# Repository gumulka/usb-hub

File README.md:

# USB Hub

A simple USB 2.0 USB-Hub, with physical buttons to toggle the power to
the port as well as an usb interface to toggle the different ports.

## Compile firmware

The firmware is written with [zephyr](zephyr).
Click [here](zephyr_getting_started) for information on how to
[get started](zephyr_getting_started).

With zephyr and west installed execute the following to compile and flash the
firmware with debug information.

```bash
west init -m https://github.com/gumulka/usb-hub --mr zephyr usb-hub
cd usb-hub
west update
cd usb-hub
west build -p -b fabians_usb_hub app -- -DOVERLAY_CONFIG="debug.conf"
west flash
```

## Compile the bootloader

The bootloader uses a lot of memory and needs some special attention to get it
to work. We are nearing the limit of what the STM32 can do and process.

Compile and flash it with the following commands:

```bash
west build -p -b fabians_usb_hub -d build_mcuboot ../bootloader/mcuboot/boot/zephyr/ -- -DOVERLAY_CONFIG="`pwd`/mcuboot.conf"
west flash -d build_mcuboot
```

[zephyr]: https://github.com/zephyrproject-rtos/zephyr
[zephyr_getting_started]: https://docs.zephyrproject.org/latest/develop/getting_started/index.html

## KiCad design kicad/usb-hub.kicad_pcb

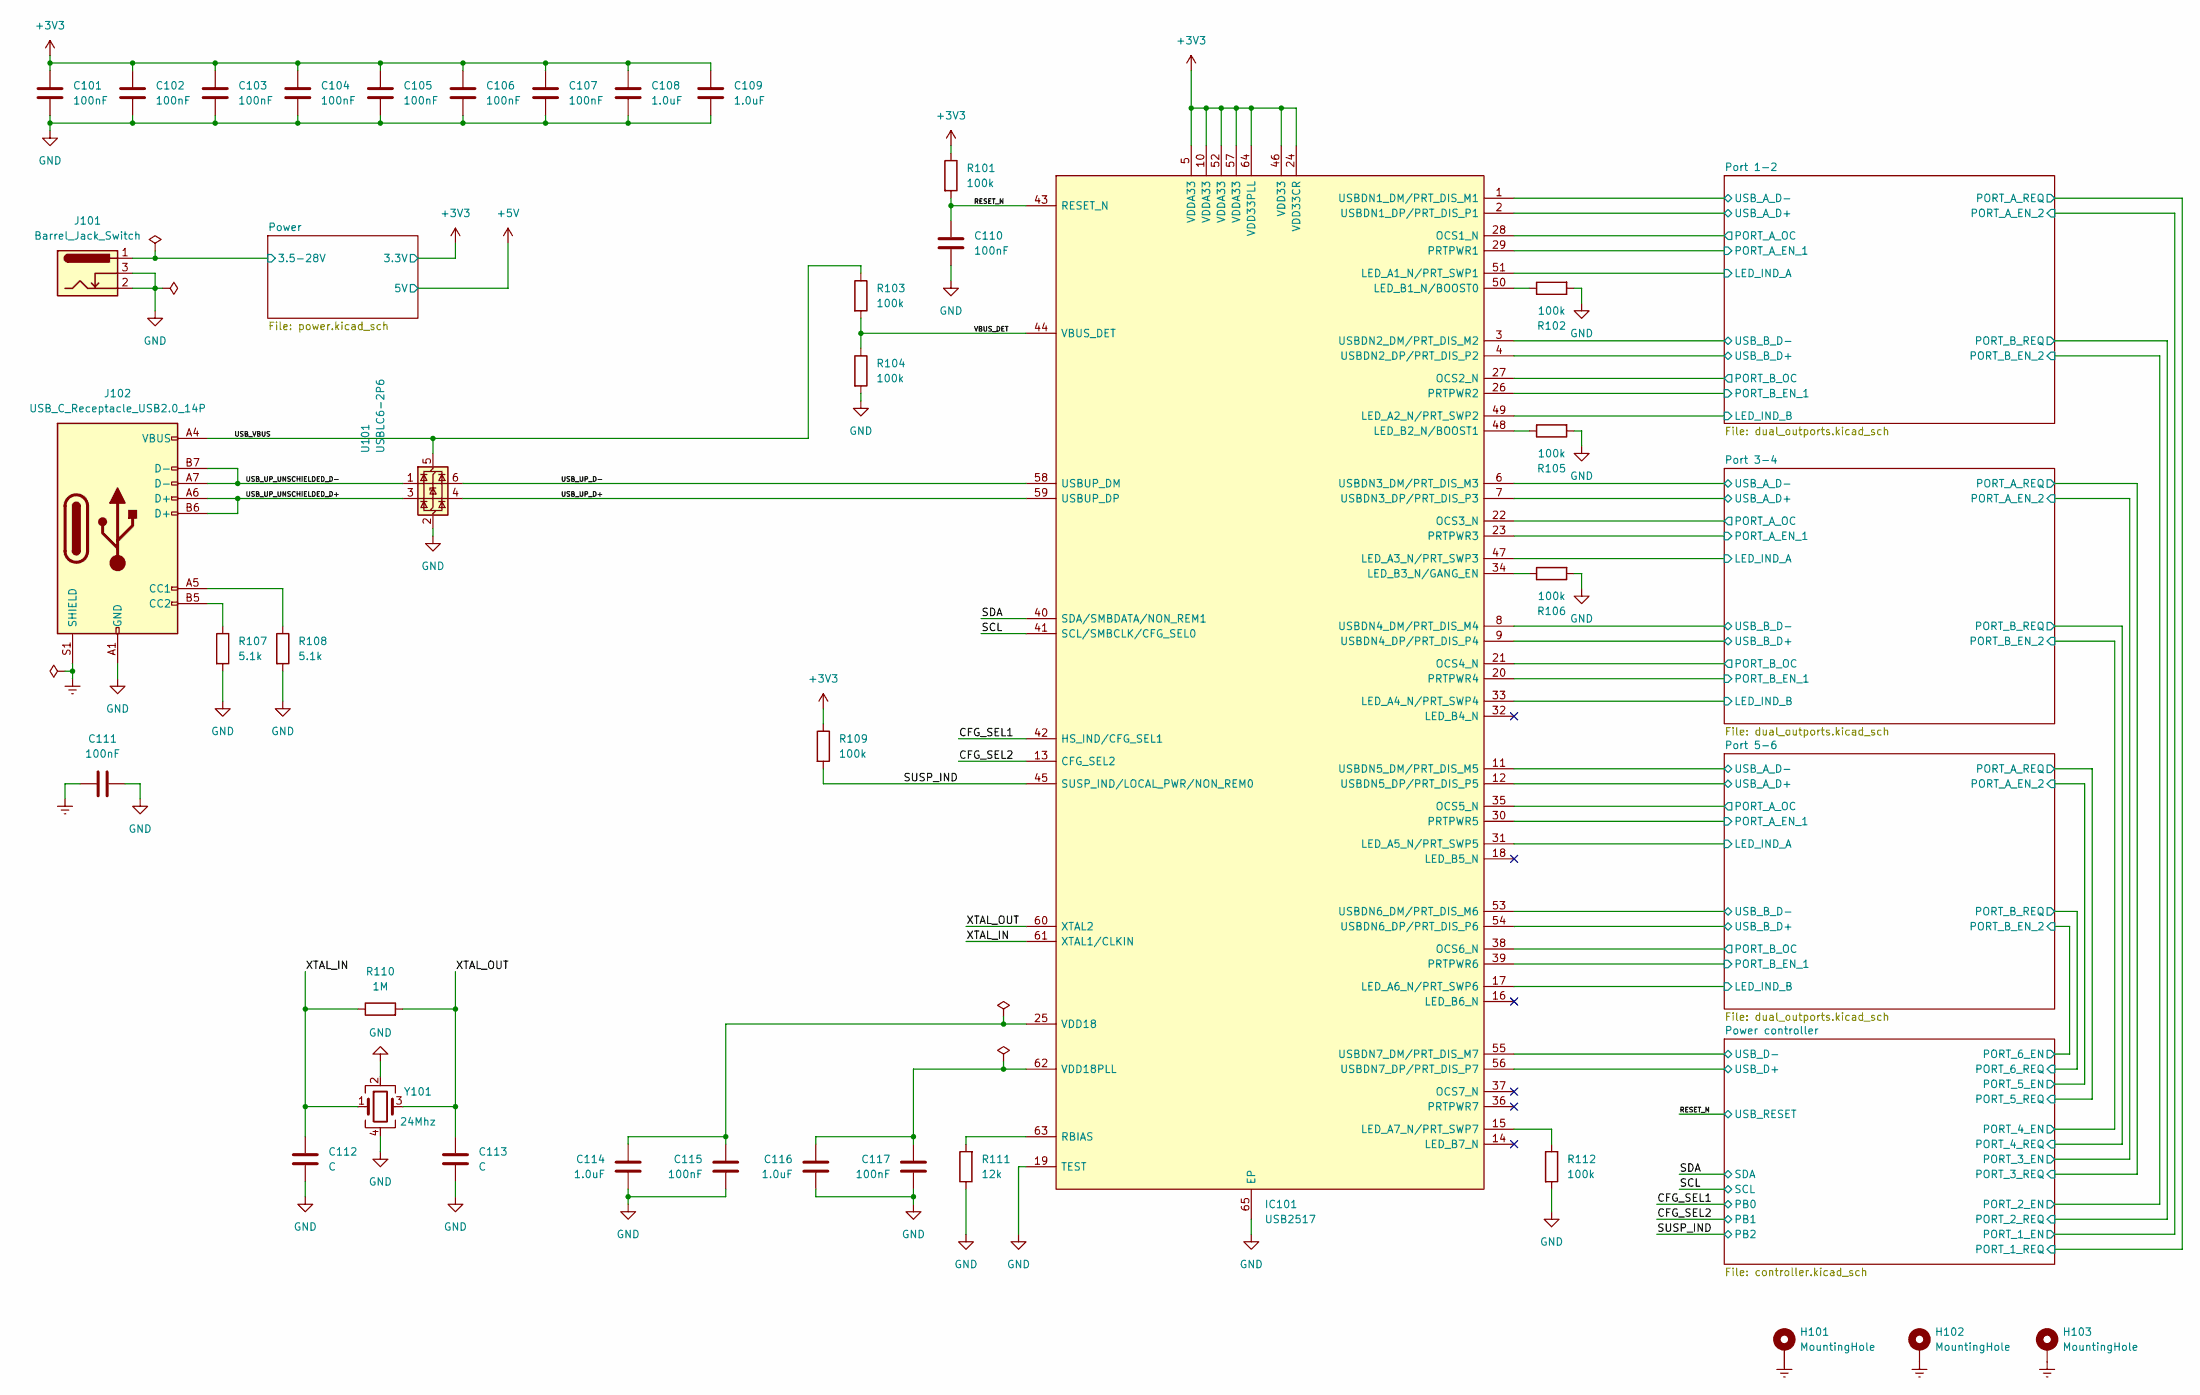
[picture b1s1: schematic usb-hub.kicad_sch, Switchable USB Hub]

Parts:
C101, C102, C103, C104, C105, C106, C107, C110, C111, C115, C117: 100nF; C_0402_1005Metric; LCSC# C307331
C108, C109, C114, C116: 1.0uF; C_0603_1608Metric; LCSC# C15849
C112, C113: C; C_0402_1005Metric
H101, H102, H103: MountingHole; MountingHole_3.2mm_M3_Pad_Via
IC101: USB2517; QFN-64-1EP_9x9mm_P0.5mm_EP4.7x4.7mm_ThermalVias; MPN USB2517; LCSC# C626668
J101: Barrel_Jack_Switch; BarrelJack_Wuerth_6941xx301002; MPN 694106301002
J102: USB_C_Receptacle_USB2.0_14P; USB_C_Receptacle_G-Switch_GT-USB-7010ASV; LCSC# C2988369
R101, R102, R103, R104, R105, R106, R109, R112: 100k; R_0402_1005Metric; MPN 100K; LCSC# C25741
R107, R108: 5.1k; R_0402_1005Metric; MPN 5,1K; LCSC# C25905
R110: 1M; R_0402_1005Metric; MPN 1M; LCSC# C26083
R111: 12k; R_0402_1005Metric; MPN 12K; LCSC# C25752
U101: USBLC6-2P6; SOT-666; MPN USBLC6-2P6; LCSC# C2827693
Y101: 24Mhz; Crystal_SMD_3225-4Pin_3.2x2.5mm; LCSC# C70590

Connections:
+3V3: C101.1, C102.1, C103.1, C104.1, C105.1, C106.1, C107.1, C108.1, C109.1, IC101.5 (VDDA33), IC101.10 (VDDA33), IC101.24 (VDD33CR), IC101.46 (VDD33), IC101.52 (VDDA33), IC101.57 (VDDA33), IC101.64 (VDD33PLL), R101.1, R109.1; also elsewhere on the board
/CFG_SEL1: IC101.42 (HS_IND/CFG_SEL1); also elsewhere on the board
/CFG_SEL2: IC101.13 (CFG_SEL2); also elsewhere on the board
/Port 1-2/LED_IND_A: IC101.51 (LED_A1_N/PRT_SWP1); also elsewhere on the board
/Port 1-2/LED_IND_B: IC101.49 (LED_A2_N/PRT_SWP2); also elsewhere on the board
/Port 1-2/PORT_A_EN_1: IC101.29 (PRTPWR1); also elsewhere on the board
/Port 1-2/PORT_A_OC: IC101.28 (OCS1_N); also elsewhere on the board
/Port 1-2/PORT_B_EN_1: IC101.26 (PRTPWR2); also elsewhere on the board
/Port 1-2/PORT_B_OC: IC101.27 (OCS2_N); also elsewhere on the board
/Port 1-2/USB_A_D+: IC101.2 (USBDN1_DP/PRT_DIS_P1); also elsewhere on the board
/Port 1-2/USB_A_D-: IC101.1 (USBDN1_DM/PRT_DIS_M1); also elsewhere on the board
/Port 1-2/USB_B_D+: IC101.4 (USBDN2_DP/PRT_DIS_P2); also elsewhere on the board
/Port 1-2/USB_B_D-: IC101.3 (USBDN2_DM/PRT_DIS_M2); also elsewhere on the board
/Port 3-4/LED_IND_A: IC101.47 (LED_A3_N/PRT_SWP3); also elsewhere on the board
/Port 3-4/LED_IND_B: IC101.33 (LED_A4_N/PRT_SWP4); also elsewhere on the board
/Port 3-4/PORT_A_EN_1: IC101.23 (PRTPWR3); also elsewhere on the board
/Port 3-4/PORT_A_OC: IC101.22 (OCS3_N); also elsewhere on the board
/Port 3-4/PORT_B_EN_1: IC101.20 (PRTPWR4); also elsewhere on the board
/Port 3-4/PORT_B_OC: IC101.21 (OCS4_N); also elsewhere on the board
/Port 3-4/USB_A_D+: IC101.7 (USBDN3_DP/PRT_DIS_P3); also elsewhere on the board
/Port 3-4/USB_A_D-: IC101.6 (USBDN3_DM/PRT_DIS_M3); also elsewhere on the board
/Port 3-4/USB_B_D+: IC101.9 (USBDN4_DP/PRT_DIS_P4); also elsewhere on the board
/Port 3-4/USB_B_D-: IC101.8 (USBDN4_DM/PRT_DIS_M4); also elsewhere on the board
/Port 5-6/LED_IND_A: IC101.31 (LED_A5_N/PRT_SWP5); also elsewhere on the board
/Port 5-6/LED_IND_B: IC101.17 (LED_A6_N/PRT_SWP6); also elsewhere on the board
/Port 5-6/PORT_A_EN_1: IC101.30 (PRTPWR5); also elsewhere on the board
/Port 5-6/PORT_A_OC: IC101.35 (OCS5_N); also elsewhere on the board
/Port 5-6/PORT_B_EN_1: IC101.39 (PRTPWR6); also elsewhere on the board
/Port 5-6/PORT_B_OC: IC101.38 (OCS6_N); also elsewhere on the board
/Port 5-6/USB_A_D+: IC101.12 (USBDN5_DP/PRT_DIS_P5); also elsewhere on the board
/Port 5-6/USB_A_D-: IC101.11 (USBDN5_DM/PRT_DIS_M5); also elsewhere on the board
/Port 5-6/USB_B_D+: IC101.54 (USBDN6_DP/PRT_DIS_P6); also elsewhere on the board
/Port 5-6/USB_B_D-: IC101.53 (USBDN6_DM/PRT_DIS_M6); also elsewhere on the board
/Power controller/USB_D+: IC101.56 (USBDN7_DP/PRT_DIS_P7); also elsewhere on the board
/Power controller/USB_D-: IC101.55 (USBDN7_DM/PRT_DIS_M7); also elsewhere on the board
/Power/3.5-28V: J101.1; also elsewhere on the board
/RESET_N: C110.1, IC101.43 (RESET_N), R101.2; also elsewhere on the board
/SCL: IC101.41 (SCL/SMBCLK/CFG_SEL0); also elsewhere on the board
/SDA: IC101.40 (SDA/SMBDATA/NON_REM1); also elsewhere on the board
/SUSP_IND: IC101.45 (SUSP_IND/LOCAL_PWR/NON_REM0), R109.2; also elsewhere on the board
/USB_UP_D+: IC101.59 (USBUP_DP), U101.4 (I/O2)
/USB_UP_D-: IC101.58 (USBUP_DM), U101.6 (I/O1)
/USB_UP_UNSCHIELDED_D+: J102.A6 (D+), J102.B6 (D+), U101.3 (I/O2)
/USB_UP_UNSCHIELDED_D-: J102.A7 (D-), J102.B7 (D-), U101.1 (I/O1)
/USB_VBUS: J102.A4 (VBUS), J102.A9 (VBUS), J102.B4 (VBUS), J102.B9 (VBUS), R103.1, U101.5 (VBUS)
/VBUS_DET: IC101.44 (VBUS_DET), R103.2, R104.1
/XTAL_IN: C112.1, IC101.61 (XTAL1/CLKIN), R110.1, Y101.1
/XTAL_OUT: C113.1, IC101.60 (XTAL2), R110.2, Y101.3
Earth: C111.2, H101.1, H102.1, H103.1, J102.S1 (SHIELD); also elsewhere on the board
GND: C101.2, C102.2, C103.2, C104.2, C105.2, C106.2, C107.2, C108.2, C109.2, C110.2, C111.1, C112.2, C113.2, C114.2, C115.2, C116.2, C117.2, IC101.19 (TEST), IC101.65 (EP), J101.2, J101.3, J102.A1 (GND), J102.A12 (GND), J102.B1 (GND), J102.B12 (GND), R102.2, R104.2, R105.2, R106.2, R107.2, R108.2, R111.1, R112.2, U101.2 (GND), Y101.2, Y101.4; also elsewhere on the board
unnamed: IC101.15 (LED_A7_N/PRT_SWP7), R112.1
unnamed: IC101.50 (LED_B1_N/BOOST0), R102.1
unnamed: IC101.48 (LED_B2_N/BOOST1), R105.1
unnamed: IC101.34 (LED_B3_N/GANG_EN), R106.1
unnamed: IC101.63 (RBIAS), R111.2
unnamed: C114.1, C115.1, IC101.25 (VDD18)
unnamed: C116.1, C117.1, IC101.62 (VDD18PLL)
unnamed: J102.A5 (CC1), R108.1
unnamed: J102.B5 (CC2), R107.1

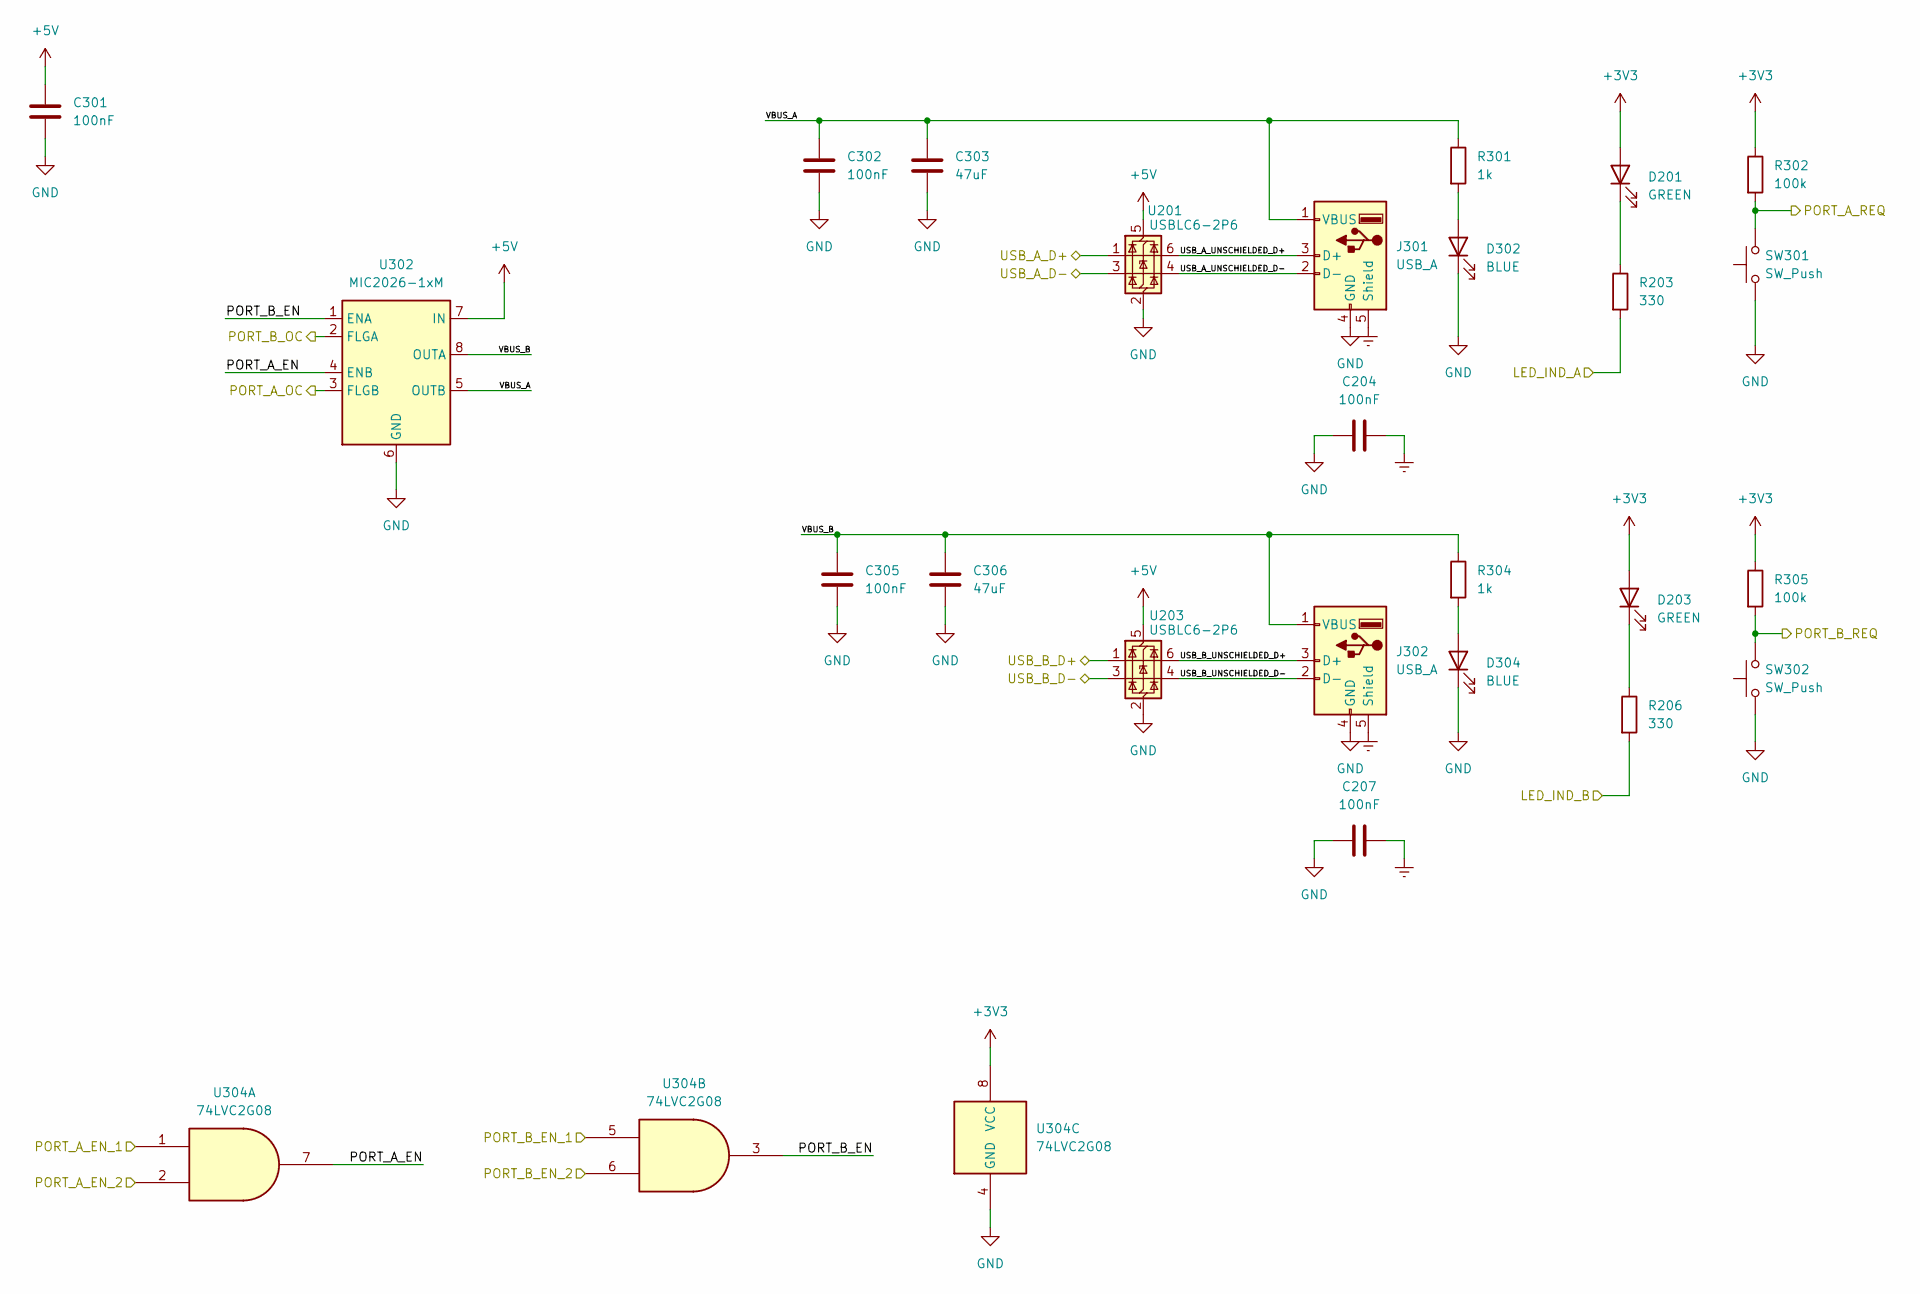
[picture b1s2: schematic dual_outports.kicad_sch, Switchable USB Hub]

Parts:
C204, C207, C301, C302, C305: 100nF; C_0402_1005Metric; LCSC# C307331
C303, C306: 47uF; C_0805_2012Metric; LCSC# C16780
D201, D203: GREEN; LED_0603_1608Metric; LCSC# C2986059
D302, D304: BLUE; LED_0603_1608Metric; LCSC# C72041
J301, J302: USB_A; UJ2-AV-W4-TH; MPN UJ2-AV-W4-TH
R203, R206: 330; R_0402_1005Metric; MPN 330R; LCSC# C25104
R301, R304: 1k; R_0402_1005Metric; MPN 1k; LCSC# C11702
R302, R305: 100k; R_0402_1005Metric; MPN 100K; LCSC# C25741
SW301, SW302: SW_Push; SW_SPST_TL3342; LCSC# C318884
U201, U203: USBLC6-2P6; SOT-666; MPN USBLC6-2P6; LCSC# C2827693
U302: MIC2026-1xM; SOIC-8_3.9x4.9mm_P1.27mm; MPN MIC2026-1YM; LCSC# C144190
U304: 74LVC2G08; VSSOP-8_2.3x2mm_P0.5mm; MPN 74LVC2G08; LCSC# C91875

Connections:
+3V3: D201.2 (A), D203.2 (A), R302.1, R305.1, U304.8 (VCC); also elsewhere on the board
+5V: C301.1, U201.5 (VBUS), U203.5 (VBUS), U302.7 (IN); also elsewhere on the board
/Port 1-2/LED_IND_A: R203.2; also elsewhere on the board
/Port 1-2/LED_IND_B: R206.2; also elsewhere on the board
/Port 1-2/USB_A_D+: U201.1 (I/O1); also elsewhere on the board
/Port 1-2/USB_A_D-: U201.3 (I/O2); also elsewhere on the board
/Port 1-2/USB_B_D+: U203.1 (I/O1); also elsewhere on the board
/Port 1-2/USB_B_D-: U203.3 (I/O2); also elsewhere on the board
/Port 3-4/PORT_A_EN: U302.4 (ENB), U304.7
/Port 3-4/PORT_A_EN_1: U304.1; also elsewhere on the board
/Port 3-4/PORT_A_EN_2: U304.2; also elsewhere on the board
/Port 3-4/PORT_A_OC: U302.3 (FLGB); also elsewhere on the board
/Port 3-4/PORT_A_REQ: R302.2, SW301.2; also elsewhere on the board
/Port 3-4/PORT_B_EN: U302.1 (ENA), U304.3
/Port 3-4/PORT_B_EN_1: U304.5; also elsewhere on the board
/Port 3-4/PORT_B_EN_2: U304.6; also elsewhere on the board
/Port 3-4/PORT_B_OC: U302.2 (FLGA); also elsewhere on the board
/Port 3-4/PORT_B_REQ: R305.2, SW302.2; also elsewhere on the board
/Port 3-4/VBUS_A: C302.1, C303.1, J301.1 (VBUS), R301.1, U302.5 (OUTB)
/Port 3-4/VBUS_B: C305.1, C306.1, J302.1 (VBUS), R304.1, U302.8 (OUTA)
Earth: C204.2, C207.2, J301.5 (Shield), J302.5 (Shield); also elsewhere on the board
GND: C204.1, C207.1, C301.2, C302.2, C303.2, C305.2, C306.2, D302.1 (K), D304.1 (K), J301.4 (GND), J302.4 (GND), SW301.1, SW302.1, U201.2 (GND), U203.2 (GND), U302.6 (GND), U304.4 (GND); also elsewhere on the board
unnamed: D201.1 (K), R203.1
unnamed: D203.1 (K), R206.1
unnamed: D302.2 (A), R301.2
unnamed: D304.2 (A), R304.2

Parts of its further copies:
C201, C202, C205, C304, C307, C401, C402, C404, C405, C407: 100nF; C_0402_1005Metric; LCSC# C307331
C203, C206, C403, C406: 47uF; C_0805_2012Metric; LCSC# C16780
D202, D204, D402, D404: BLUE; LED_0603_1608Metric; LCSC# C72041
D301, D303, D401, D403: GREEN; LED_0603_1608Metric; LCSC# C2986059
J201, J202, J401, J402: USB_A; UJ2-AV-W4-TH; MPN UJ2-AV-W4-TH
R201, R204, R401, R404: 1k; R_0402_1005Metric; MPN 1k; LCSC# C11702
R202, R205, R402, R405: 100k; R_0402_1005Metric; MPN 100K; LCSC# C25741
R303, R306, R403, R406: 330; R_0402_1005Metric; MPN 330R; LCSC# C25104
SW201, SW202, SW401, SW402: SW_Push; SW_SPST_TL3342; LCSC# C318884
U202, U402: MIC2026-1xM; SOIC-8_3.9x4.9mm_P1.27mm; MPN MIC2026-1YM; LCSC# C144190
U204, U404: 74LVC2G08; VSSOP-8_2.3x2mm_P0.5mm; MPN 74LVC2G08; LCSC# C91875
U301, U303, U401, U403: USBLC6-2P6; SOT-666; MPN USBLC6-2P6; LCSC# C2827693

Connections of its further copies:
+3V3: D301.2 (A), D303.2 (A), D401.2 (A), D403.2 (A), R202.1, R205.1, R402.1, R405.1, U204.8 (VCC), U404.8 (VCC); also elsewhere on the board
+5V: C201.1, C401.1, U202.7 (IN), U301.5 (VBUS), U303.5 (VBUS), U401.5 (VBUS), U402.7 (IN), U403.5 (VBUS); also elsewhere on the board
/Port 1-2/PORT_A_EN: U202.4 (ENB), U204.7
/Port 1-2/PORT_A_EN_1: U204.1; also elsewhere on the board
/Port 1-2/PORT_A_EN_2: U204.2; also elsewhere on the board
/Port 1-2/PORT_A_OC: U202.3 (FLGB); also elsewhere on the board
/Port 1-2/PORT_A_REQ: R202.2, SW201.2; also elsewhere on the board
/Port 1-2/PORT_B_EN: U202.1 (ENA), U204.3
/Port 1-2/PORT_B_EN_1: U204.5; also elsewhere on the board
/Port 1-2/PORT_B_EN_2: U204.6; also elsewhere on the board
/Port 1-2/PORT_B_OC: U202.2 (FLGA); also elsewhere on the board
/Port 1-2/PORT_B_REQ: R205.2, SW202.2; also elsewhere on the board
/Port 1-2/VBUS_A: C202.1, C203.1, J201.1 (VBUS), R201.1, U202.5 (OUTB)
/Port 1-2/VBUS_B: C205.1, C206.1, J202.1 (VBUS), R204.1, U202.8 (OUTA)
/Port 3-4/LED_IND_A: R303.2; also elsewhere on the board
/Port 3-4/LED_IND_B: R306.2; also elsewhere on the board
/Port 3-4/USB_A_D+: U301.1 (I/O1); also elsewhere on the board
/Port 3-4/USB_A_D-: U301.3 (I/O2); also elsewhere on the board
/Port 3-4/USB_B_D+: U303.1 (I/O1); also elsewhere on the board
/Port 3-4/USB_B_D-: U303.3 (I/O2); also elsewhere on the board
/Port 5-6/LED_IND_A: R403.2; also elsewhere on the board
/Port 5-6/LED_IND_B: R406.2; also elsewhere on the board
/Port 5-6/PORT_A_EN: U402.4 (ENB), U404.7
/Port 5-6/PORT_A_EN_1: U404.1; also elsewhere on the board
/Port 5-6/PORT_A_EN_2: U404.2; also elsewhere on the board
/Port 5-6/PORT_A_OC: U402.3 (FLGB); also elsewhere on the board
/Port 5-6/PORT_A_REQ: R402.2, SW401.2; also elsewhere on the board
/Port 5-6/PORT_B_EN: U402.1 (ENA), U404.3
/Port 5-6/PORT_B_EN_1: U404.5; also elsewhere on the board
/Port 5-6/PORT_B_EN_2: U404.6; also elsewhere on the board
/Port 5-6/PORT_B_OC: U402.2 (FLGA); also elsewhere on the board
/Port 5-6/PORT_B_REQ: R405.2, SW402.2; also elsewhere on the board
/Port 5-6/USB_A_D+: U401.1 (I/O1); also elsewhere on the board
/Port 5-6/USB_A_D-: U401.3 (I/O2); also elsewhere on the board
/Port 5-6/USB_A_UNSCHIELDED_D+: J401.3 (D+), U401.6 (I/O1)
/Port 5-6/USB_A_UNSCHIELDED_D-: J401.2 (D-), U401.4 (I/O2)
/Port 5-6/USB_B_D+: U403.1 (I/O1); also elsewhere on the board
/Port 5-6/USB_B_D-: U403.3 (I/O2); also elsewhere on the board
/Port 5-6/USB_B_UNSCHIELDED_D+: J402.3 (D+), U403.6 (I/O1)
/Port 5-6/USB_B_UNSCHIELDED_D-: J402.2 (D-), U403.4 (I/O2)
/Port 5-6/VBUS_A: C402.1, C403.1, J401.1 (VBUS), R401.1, U402.5 (OUTB)
/Port 5-6/VBUS_B: C405.1, C406.1, J402.1 (VBUS), R404.1, U402.8 (OUTA)
Earth: C304.2, C307.2, C404.2, C407.2, J201.5 (Shield), J202.5 (Shield), J401.5 (Shield), J402.5 (Shield); also elsewhere on the board
GND: C201.2, C202.2, C203.2, C205.2, C206.2, C304.1, C307.1, C401.2, C402.2, C403.2, C404.1, C405.2, C406.2, C407.1, D202.1 (K), D204.1 (K), D402.1 (K), D404.1 (K), J201.4 (GND), J202.4 (GND), J401.4 (GND), J402.4 (GND), SW201.1, SW202.1, SW401.1, SW402.1, U202.6 (GND), U204.4 (GND), U301.2 (GND), U303.2 (GND), U401.2 (GND), U402.6 (GND), U403.2 (GND), U404.4 (GND); also elsewhere on the board
unnamed: D202.2 (A), R201.2
unnamed: D204.2 (A), R204.2
unnamed: D301.1 (K), R303.1
unnamed: D303.1 (K), R306.1
unnamed: D401.1 (K), R403.1
unnamed: D402.2 (A), R401.2
unnamed: D403.1 (K), R406.1
unnamed: D404.2 (A), R404.2

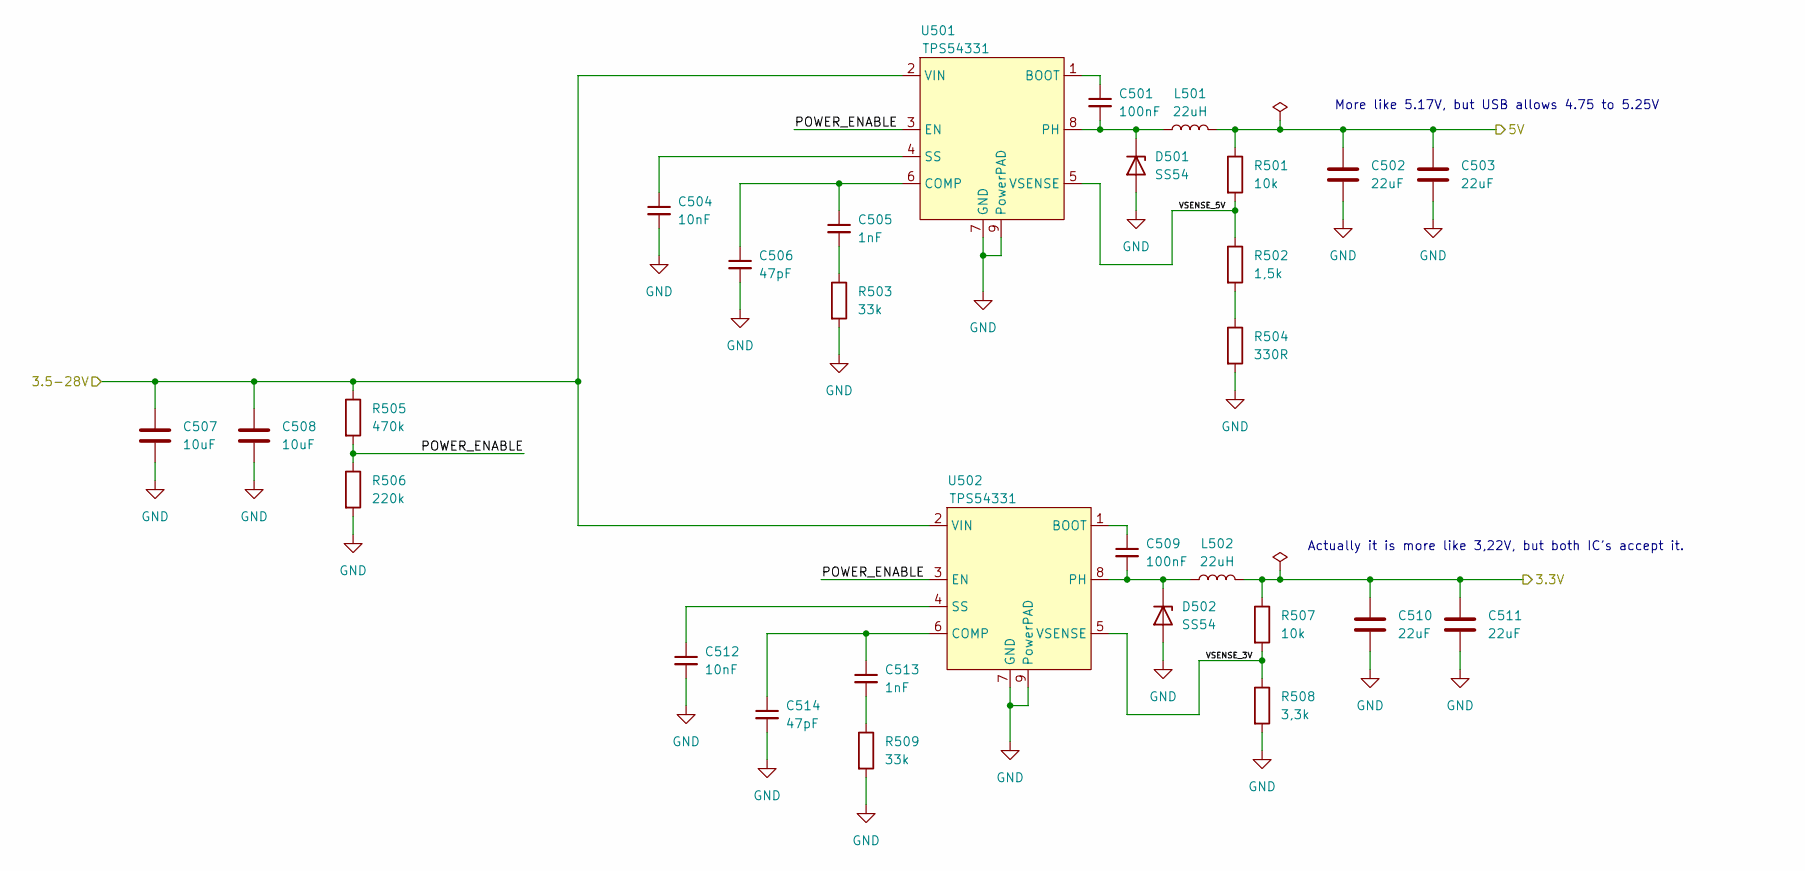
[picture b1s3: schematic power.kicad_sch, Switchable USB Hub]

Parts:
C501, C509: 100nF; C_0402_1005Metric; LCSC# C307331
C502, C503, C510, C511: 22uF; C_0603_1608Metric; MPN 6.3V 22uF; LCSC# C59461
C504, C512: 10nF; C_0402_1005Metric; LCSC# C15195
C505, C513: 1nF; C_0402_1005Metric; LCSC# C1523
C506, C514: 47pF; C_0402_1005Metric; LCSC# C1567
C507, C508: 10uF; C_0805_2012Metric; MPN 50V 10uF; LCSC# C440198
D501, D502: SS54; D_SMA; LCSC# C22452
L501, L502: 22uH; YSPI0630A; MPN 3A 22uH; LCSC# C497873
R501, R507: 10k; R_0402_1005Metric; MPN 10k; LCSC# C25744
R502: 1,5k; R_0402_1005Metric; MPN 1,5k; LCSC# C25867
R503, R509: 33k; R_0402_1005Metric; MPN 33k; LCSC# C25779
R504: 330R; R_0402_1005Metric; MPN 330R; LCSC# C25104
R505: 470k; R_0402_1005Metric; MPN 470k; LCSC# C25790
R506: 220k; R_0402_1005Metric; MPN 220k; LCSC# C25767
R508: 3,3k; R_0402_1005Metric; MPN 3,3k; LCSC# C25890
U501, U502: TPS54331; SOIC-8-1EP_3.9x4.9mm_P1.27mm_EP2.29x3mm_ThermalVias; MPN TPS54331; LCSC# C9865

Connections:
+3V3: C510.1, C511.1, L502.2, R507.1; also elsewhere on the board
+5V: C502.1, C503.1, L501.2, R501.1; also elsewhere on the board
/Power/3.5-28V: C507.1, C508.1, R505.1, U501.2 (VIN), U502.2 (VIN); also elsewhere on the board
/Power/POWER_ENABLE: R505.2, R506.1, U501.3 (EN), U502.3 (EN)
/Power/VSENSE_3V: R507.2, R508.1, U502.5 (VSENSE)
/Power/VSENSE_5V: R501.2, R502.1, U501.5 (VSENSE)
GND: C502.2, C503.2, C504.2, C506.2, C507.2, C508.2, C510.2, C511.2, C512.2, C514.2, D501.2 (A), D502.2 (A), R503.2, R504.2, R506.2, R508.2, R509.2, U501.7 (GND), U501.9 (PowerPAD), U502.7 (GND), U502.9 (PowerPAD); also elsewhere on the board
unnamed: C505.2, R503.1
unnamed: C513.2, R509.1
unnamed: C501.2, D501.1 (K), L501.1, U501.8 (PH)
unnamed: C509.2, D502.1 (K), L502.1, U502.8 (PH)
unnamed: R502.2, R504.1
unnamed: C501.1, U501.1 (BOOT)
unnamed: C505.1, C506.1, U501.6 (COMP)
unnamed: C504.1, U501.4 (SS)
unnamed: C509.1, U502.1 (BOOT)
unnamed: C513.1, C514.1, U502.6 (COMP)
unnamed: C512.1, U502.4 (SS)

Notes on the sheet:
Actually it is more like 3,22V, but both IC's accept it.
More like 5.17V, but USB allows 4.75 to 5.25V

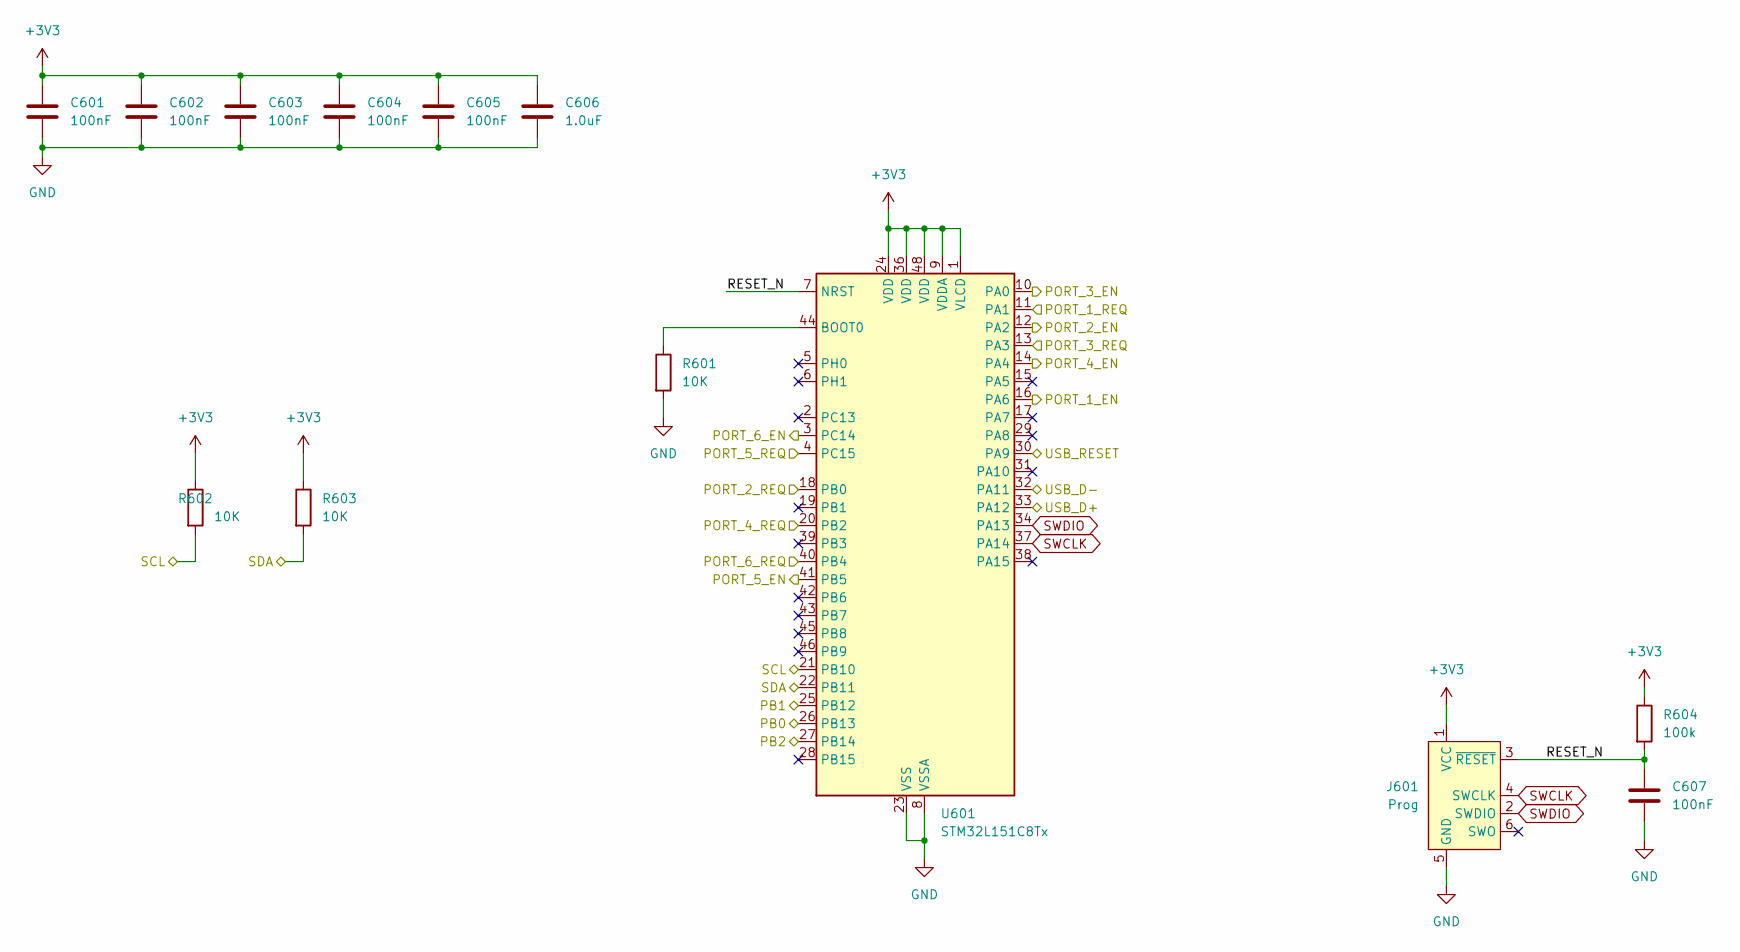
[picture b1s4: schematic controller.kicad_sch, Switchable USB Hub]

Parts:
C601, C602, C603, C604, C605, C607: 100nF; C_0402_1005Metric; LCSC# C307331
C606: 1.0uF; C_0603_1608Metric; LCSC# C15849
J601: Prog; Tag-Connect_TC2030-IDC-NL_2x03_P1.27mm_Vertical
R601, R602, R603: 10K; R_0402_1005Metric; MPN 10k; LCSC# C25744
R604: 100k; R_0402_1005Metric; MPN 100K; LCSC# C25741
U601: STM32L151C8Tx; LQFP-48_7x7mm_P0.5mm; MPN STM32L151C8T6; LCSC# C9861

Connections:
+3V3: C601.1, C602.1, C603.1, C604.1, C605.1, C606.1, J601.1 (VCC), R602.1, R603.1, R604.1, U601.1 (VLCD), U601.9 (VDDA), U601.24 (VDD), U601.36 (VDD), U601.48 (VDD); also elsewhere on the board
/CFG_SEL1: U601.26 (PB13); also elsewhere on the board
/CFG_SEL2: U601.25 (PB12); also elsewhere on the board
/Port 1-2/PORT_A_EN_2: U601.16 (PA6); also elsewhere on the board
/Port 1-2/PORT_A_REQ: U601.11 (PA1); also elsewhere on the board
/Port 1-2/PORT_B_EN_2: U601.12 (PA2); also elsewhere on the board
/Port 1-2/PORT_B_REQ: U601.18 (PB0); also elsewhere on the board
/Port 3-4/PORT_A_EN_2: U601.10 (PA0); also elsewhere on the board
/Port 3-4/PORT_A_REQ: U601.13 (PA3); also elsewhere on the board
/Port 3-4/PORT_B_EN_2: U601.14 (PA4); also elsewhere on the board
/Port 3-4/PORT_B_REQ: U601.20 (PB2); also elsewhere on the board
/Port 5-6/PORT_A_EN_2: U601.41 (PB5); also elsewhere on the board
/Port 5-6/PORT_A_REQ: U601.4 (PC15); also elsewhere on the board
/Port 5-6/PORT_B_EN_2: U601.3 (PC14); also elsewhere on the board
/Port 5-6/PORT_B_REQ: U601.40 (PB4); also elsewhere on the board
/Power controller/RESET_N: C607.1, J601.3 (~RESET), R604.2, U601.7 (NRST)
/Power controller/USB_D+: U601.33 (PA12); also elsewhere on the board
/Power controller/USB_D-: U601.32 (PA11); also elsewhere on the board
/RESET_N: U601.30 (PA9); also elsewhere on the board
/SCL: R602.2, U601.21 (PB10); also elsewhere on the board
/SDA: R603.2, U601.22 (PB11); also elsewhere on the board
/SUSP_IND: U601.27 (PB14); also elsewhere on the board
GND: C601.2, C602.2, C603.2, C604.2, C605.2, C606.2, C607.2, J601.5 (GND), R601.2, U601.8 (VSSA), U601.23 (VSS), U601.35 (VSS), U601.47 (VSS); also elsewhere on the board
unnamed: R601.1, U601.44 (BOOT0)
SWCLK: J601.4 (SWCLK), U601.37 (PA14)
SWDIO: J601.2 (SWDIO), U601.34 (PA13)

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
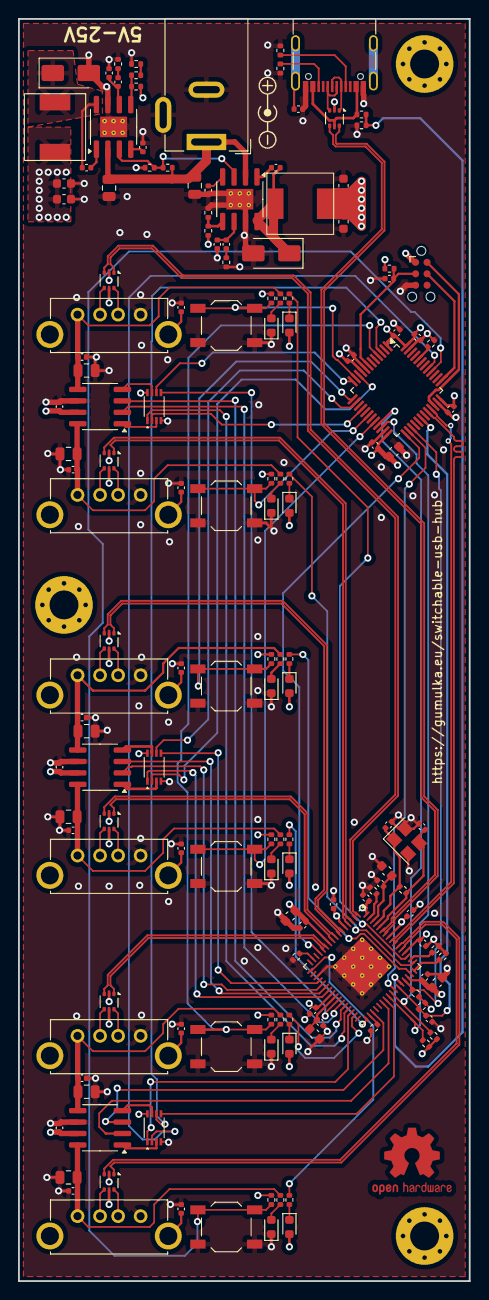
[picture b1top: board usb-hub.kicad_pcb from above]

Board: 4 copper layers, 50.0 x 140.0 mm, 154 parts (0 on the bottom side), 126 nets.

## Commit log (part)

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2024-02-28 Initial Idea with 12 ports
2024-03-02 Add power management
    And also some random stuff here and there
2024-03-02 Refine connectors and overall shape
    Replace USB connectors, because of availability.
    Use available barrel jack and USB-C connector instead of generic ones.
    Update 3D Models
    Refine rough placement of parts and board outline
2024-03-16 Add preliminary routing
    Add routing for power paths - 3.3V, 5V and Input power
    Add routing close to USB-Ports
    Mising routing for main IC's and differntial pair routing
2024-03-17 Finish first routing
    Routed everything, so that the DRC and ERC do not show anything.
2024-03-18 Improve routing
2024-03-20 Update to new enviroment
    Kicad 8 & global symbols and footprint library
2024-03-20 Generate output files
2024-04-12 Add case for USB Hub
    Designed a preliminary case with FreeCAD
2024-04-14 Add zephyr project structure
2024-08-23 Add driver for usb hub ports
    I thought about creating one instance per port, with only one gpio for
    request and enable per port, but decided against it, because it would
    be inconvenient to write the devicetree for them.
    Will maybe change later, but want to save what I have working now.
2024-08-24 fixup! Add zephyr project structure
2024-08-24 Add support for MCUboot
    Using MCUboot with two fallbacks if the device ever gets stuck.
    A: If there is no bootable application, the bootloader goes into
    USB DFU mode.
    B: If the Button for USB-Port 6 is pressed during boot, the bootloader
    goes into USB DFU mode.
    This way, there is always a way to upgrade the firmware on the STM if
2025-01-08 Make the USB-Hub somewhat work
    Not getting the features I initially wanted, but this is a working way.
    It just works as a USB-Hub, but that should be enough for now as a
    starting point.
2025-01-08 Using L151 again
    Not using USB anymore, therefore using the L151 is fine.
